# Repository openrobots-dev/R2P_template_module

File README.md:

R2P_module_template
===================

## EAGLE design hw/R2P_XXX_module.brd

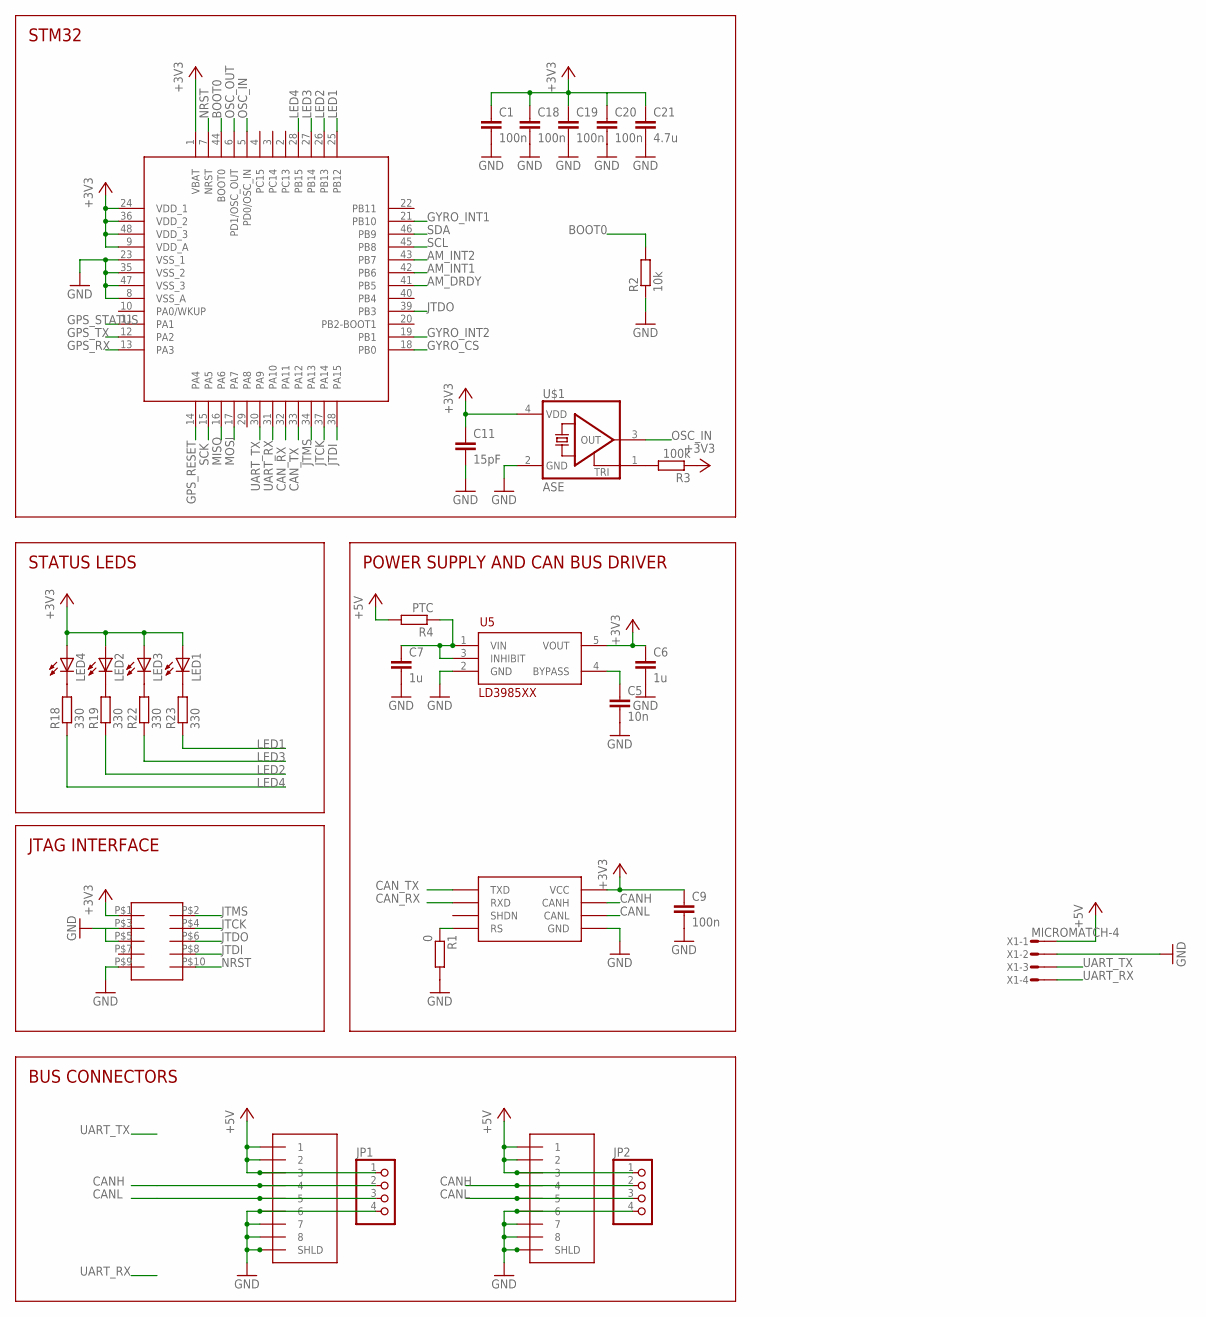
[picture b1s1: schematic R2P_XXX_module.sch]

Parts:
1, 2: RJ45-43860; 0438600010
C1, C9, C18, C19, C20: 100n; C0603
C5: 10n; C0603
C6, C7: 1u; C0603
C11: 15pF; C0603
C21: 4.7u; C0805
JP1, JP2: PINHD-1X4; 1X04
LED1, LED2, LED3, LED4: LEDCHIPLED_0805; CHIPLED_0805
R1: 0; R0603
R2: 10k; R0603
R3: 100k; R0603
R4: PTC; R0603
R18, R19, R22, R23: 330; R0603
SOT1: MAX3051; SOT23-8L
U1: STM32F103CX; LQFP48
U5: LD3985XX; SOT23-5L
U$1: ASE
U$4: FTSH-105
X1: MICROMATCH-4

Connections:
+3V3: C1.1, C6.1, C9.1, C11.1, C18.1, C19.1, C20.1, C21.1, LED1.A, LED2.A, LED3.A, LED4.A, R3.1, SOT1.P$3 (VCC), U1.1 (VBAT), U1.9 (VDD_A), U1.24 (VDD_1), U1.36 (VDD_2), U1.48 (VDD_3), U5.5 (VOUT), U$1.4 (VDD), U$4.P$1
+5V: 1.P$1 (1), 1.P$2 (2), 1.P$3 (3), 2.P$1 (1), 2.P$2 (2), 2.P$3 (3), JP1.1, JP2.1, R4.2, X1.1
AM_DRDY: U1.41 (PB5)
AM_INT1: U1.42 (PB6)
AM_INT2: U1.43 (PB7)
BOOT0: R2.2, U1.44 (BOOT0)
CANH: 1.P$4 (4), 2.P$4 (4), JP1.2, JP2.2, SOT1.P$7 (CANH)
CANL: 1.P$5 (5), 2.P$5 (5), JP1.3, JP2.3, SOT1.P$6 (CANL)
CAN_RX: SOT1.P$4 (RXD), U1.32 (PA11)
CAN_TX: SOT1.P$1 (TXD), U1.33 (PA12)
GND: 1.P$6 (6), 1.P$7 (7), 1.P$8 (8), 1.P$9 (SHLD), 1.P$10, 2.P$6 (6), 2.P$7 (7), 2.P$8 (8), 2.P$9 (SHLD), 2.P$10, C1.2, C5.2, C6.2, C7.2, C9.2, C11.2, C18.2, C19.2, C20.2, C21.2, JP1.4, JP2.4, R1.2, R2.1, SOT1.P$2 (GND), U1.8 (VSS_A), U1.23 (VSS_1), U1.35 (VSS_2), U1.47 (VSS_3), U5.2 (GND), U$1.2 (GND), U$4.P$3, U$4.P$9, X1.2
GPS_RESET: U1.14 (PA4)
GPS_RX: U1.13 (PA3)
GPS_STATUS: U1.11 (PA1)
GPS_TX: U1.12 (PA2)
GYRO_CS: U1.18 (PB0)
GYRO_INT1: U1.21 (PB10)
GYRO_INT2: U1.19 (PB1)
JTCK: U1.37 (PA14), U$4.P$4
JTDI: U1.38 (PA15), U$4.P$8
JTDO: U1.39 (PB3), U$4.P$6
JTMS: U1.34 (PA13), U$4.P$2
LED1: R23.1, U1.25 (PB12)
LED2: R19.1, U1.26 (PB13)
LED3: R22.1, U1.27 (PB14)
LED4: R18.1, U1.28 (PB15)
MISO: U1.16 (PA6)
MOSI: U1.17 (PA7)
unnamed: R1.1, SOT1.P$8 (RS)
unnamed: R3.2, U$1.1 (TRI)
unnamed: C5.1, U5.4 (BYPASS)
unnamed: C7.1, R4.1, U5.1 (VIN), U5.3 (INHIBIT)
unnamed: LED4.C, R18.2
unnamed: LED2.C, R19.2
unnamed: LED3.C, R22.2
unnamed: LED1.C, R23.2
NRST: U1.7 (NRST), U$4.P$10
OSC_IN: U1.5 (PD0/OSC_IN), U$1.3 (OUT)
OSC_OUT: U1.6 (PD1/OSC_OUT)
SCK: U1.15 (PA5)
SCL: U1.45 (PB8)
SDA: U1.46 (PB9)
UART_RX: U1.31 (PA10), X1.4
UART_TX: U1.30 (PA9), X1.3

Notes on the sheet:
STM32
POWER SUPPLY AND CAN BUS DRIVER
STATUS LEDS
JTAG INTERFACE
BUS CONNECTORS

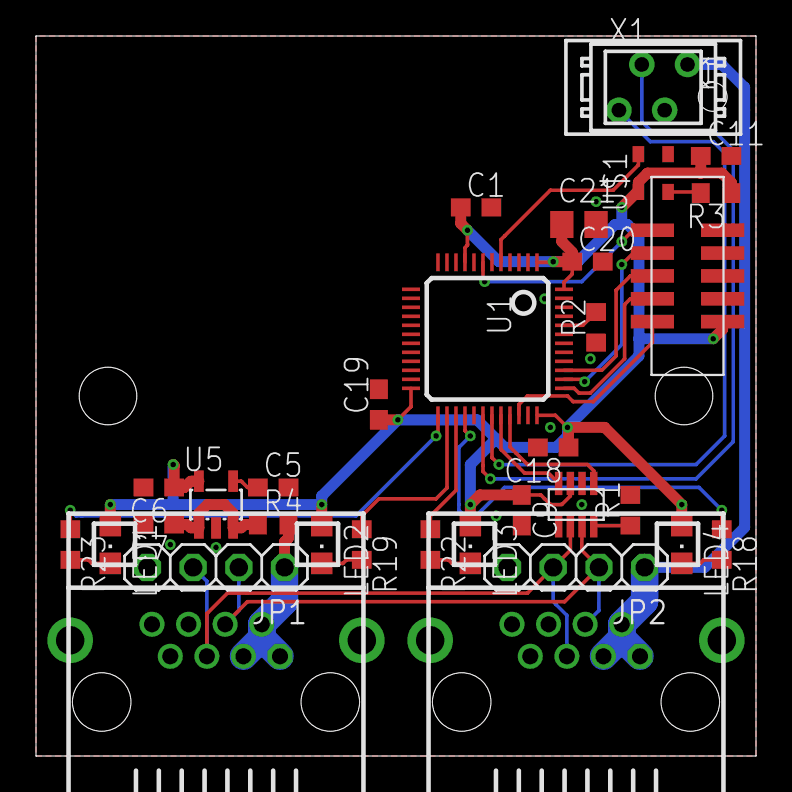
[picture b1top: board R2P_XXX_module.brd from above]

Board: 2 copper layers, 40.0 x 40.0 mm, 32 parts (0 on the bottom side), 28 nets.

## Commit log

2012-07-27 Ongoing layout
2012-07-27 Datasheets
2012-07-30 .gitignore added to revision control
2012-07-30 Board layout completed
2012-07-30 Updated micromatch connector
2012-07-31 Added space for UART connector
2012-08-01 Clock generator moved up
